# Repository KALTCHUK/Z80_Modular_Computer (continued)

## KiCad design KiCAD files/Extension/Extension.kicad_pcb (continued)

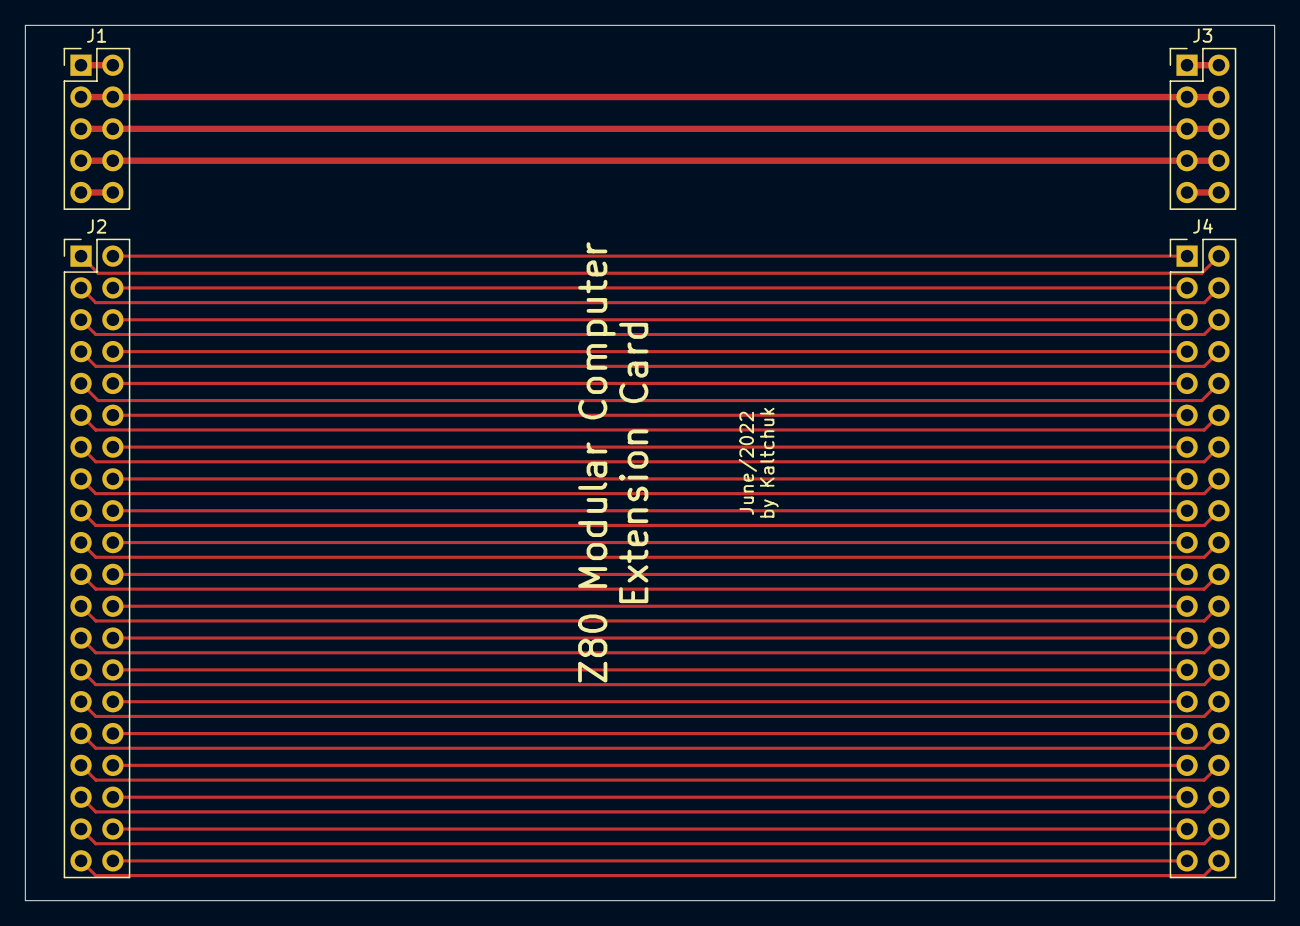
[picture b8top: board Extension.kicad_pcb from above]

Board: 2 copper layers, 99.7 x 69.8 mm, 4 parts (0 on the bottom side), 44 nets.

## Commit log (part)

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2021-09-19 office
2021-09-20 HOME
2021-09-30 Create fp-info-cache
2021-11-27 Update fp-info-cache
2022-01-12 obsolete
2022-04-21 i2c manager
2022-04-22 I2C manager 1.4
2022-04-25 i2c mgr
2022-04-29 i2cmgr 1.5
2022-05-04 i2cmgr 1.6 updates
2022-05-04 keil tests
2022-05-04 12cmgr 1.6 updates
2022-05-15 i2c tests
2022-05-15 i22 manager
2022-05-21 updates i2c_manager
2022-05-23 updated i2c manager
2022-05-24 updates i2c card
2022-05-24 pcb updates
2022-05-25 enclosure updates
2022-05-26 pcb update
2022-05-28 i2c manager fix
2022-05-31 i2c manager & enclosure updates
2022-06-01 extension card
2022-06-01 `pcbsm
2022-06-03 PCBs
2022-06-03 remove frontal
2022-06-04 esp8266 stuff
2022-06-06 office updates
2022-06-06 telnet
2022-06-07 update PCBs
2022-06-07 PCBs update
2022-06-07 Telnet updates
2022-06-07 telnet server
2022-06-08 telnet server update
2022-06-14 telnet server et ali
2022-06-15 telnet script
2022-06-18 manual update
2022-06-19 diskboot
2022-06-19 diskboot update
2022-06-24 backups/recovery
2022-06-25 recovery from doomsday
2022-07-20 esp8266 updates
2022-08-15 directory modifications.
2022-08-17 rs485
2022-08-25 gpio test
2022-08-27 8051 tests
2022-08-28 modbus tasks
2022-08-28 modbus
2022-08-28 test
2022-08-29 test for mb slave
2022-08-29 drafts
2022-08-30 mb rtu studies
2022-08-31 several tests
2022-09-01 serial tests
2022-09-01 modbus tests
2022-09-15 8051 serial tests
2022-09-27 DO-8 modbus server
2022-09-27 DO-8 schematics
2022-09-28 do8 and rs485
2022-09-29 do-8
2022-09-30 kicad
2022-10-01 DO-08
2022-10-09 DI & DO updates
2022-12-07 several modbus tests
2022-12-07 modbus sniffer
2022-12-25 i2ceeprom
2022-12-25 i2c eeprom
2022-12-26 i2c eprom
2022-12-27 misc
2023-01-02 DO-08 and PT100
2023-01-03 housekeeping
2023-01-03 ctrl
2023-01-04 pt100
2023-01-06 plc cards
2023-02-12 misc.
2023-02-13 RCבשר
2024-12-13 total commit
